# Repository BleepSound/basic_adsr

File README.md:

# Basic ADSR

Basic ADSR based on René Schmitz [Fastest envelope in the West](https://www.schmitzbits.de/adsr.html). 

Four pots, one input, one output (just what you need).

On switch to change the time constant of the ADSR. I chose some arbitrary values for the capacitors in my case, but if you want different values, you can adjust them to your needs. 

Just change the values of **C8** and **C9**, which can be either polarized electrolytic or unpolarized capacitors. Just make sure you get the orientation right on the polarized ones.

## Schematics

## BoM

[See bom](documentation/bom/Basic-ADSR_V1.0--iBoM.html)

## Build Informations

Regular build, I use ceramic capacitors but you can use film/polyester.

:warning: When building modules, always do it in this order (from smallest component to highest):
- diodes
- resistors
- DIP chips
- capacitors (film/ceramic)
- Transistors
- Electrolytic capacitors

To solder the headers, place them and place both PCBs in their final position before fully soldering the pin headers/sockets.

For the next parts, always place them without soldering them on: 
- jacks, pots and switches that go throught the front panel

Once placed, put the front panel in place, then fasten all components to it. Once this is done, you can solder all the remaining components.

## Images

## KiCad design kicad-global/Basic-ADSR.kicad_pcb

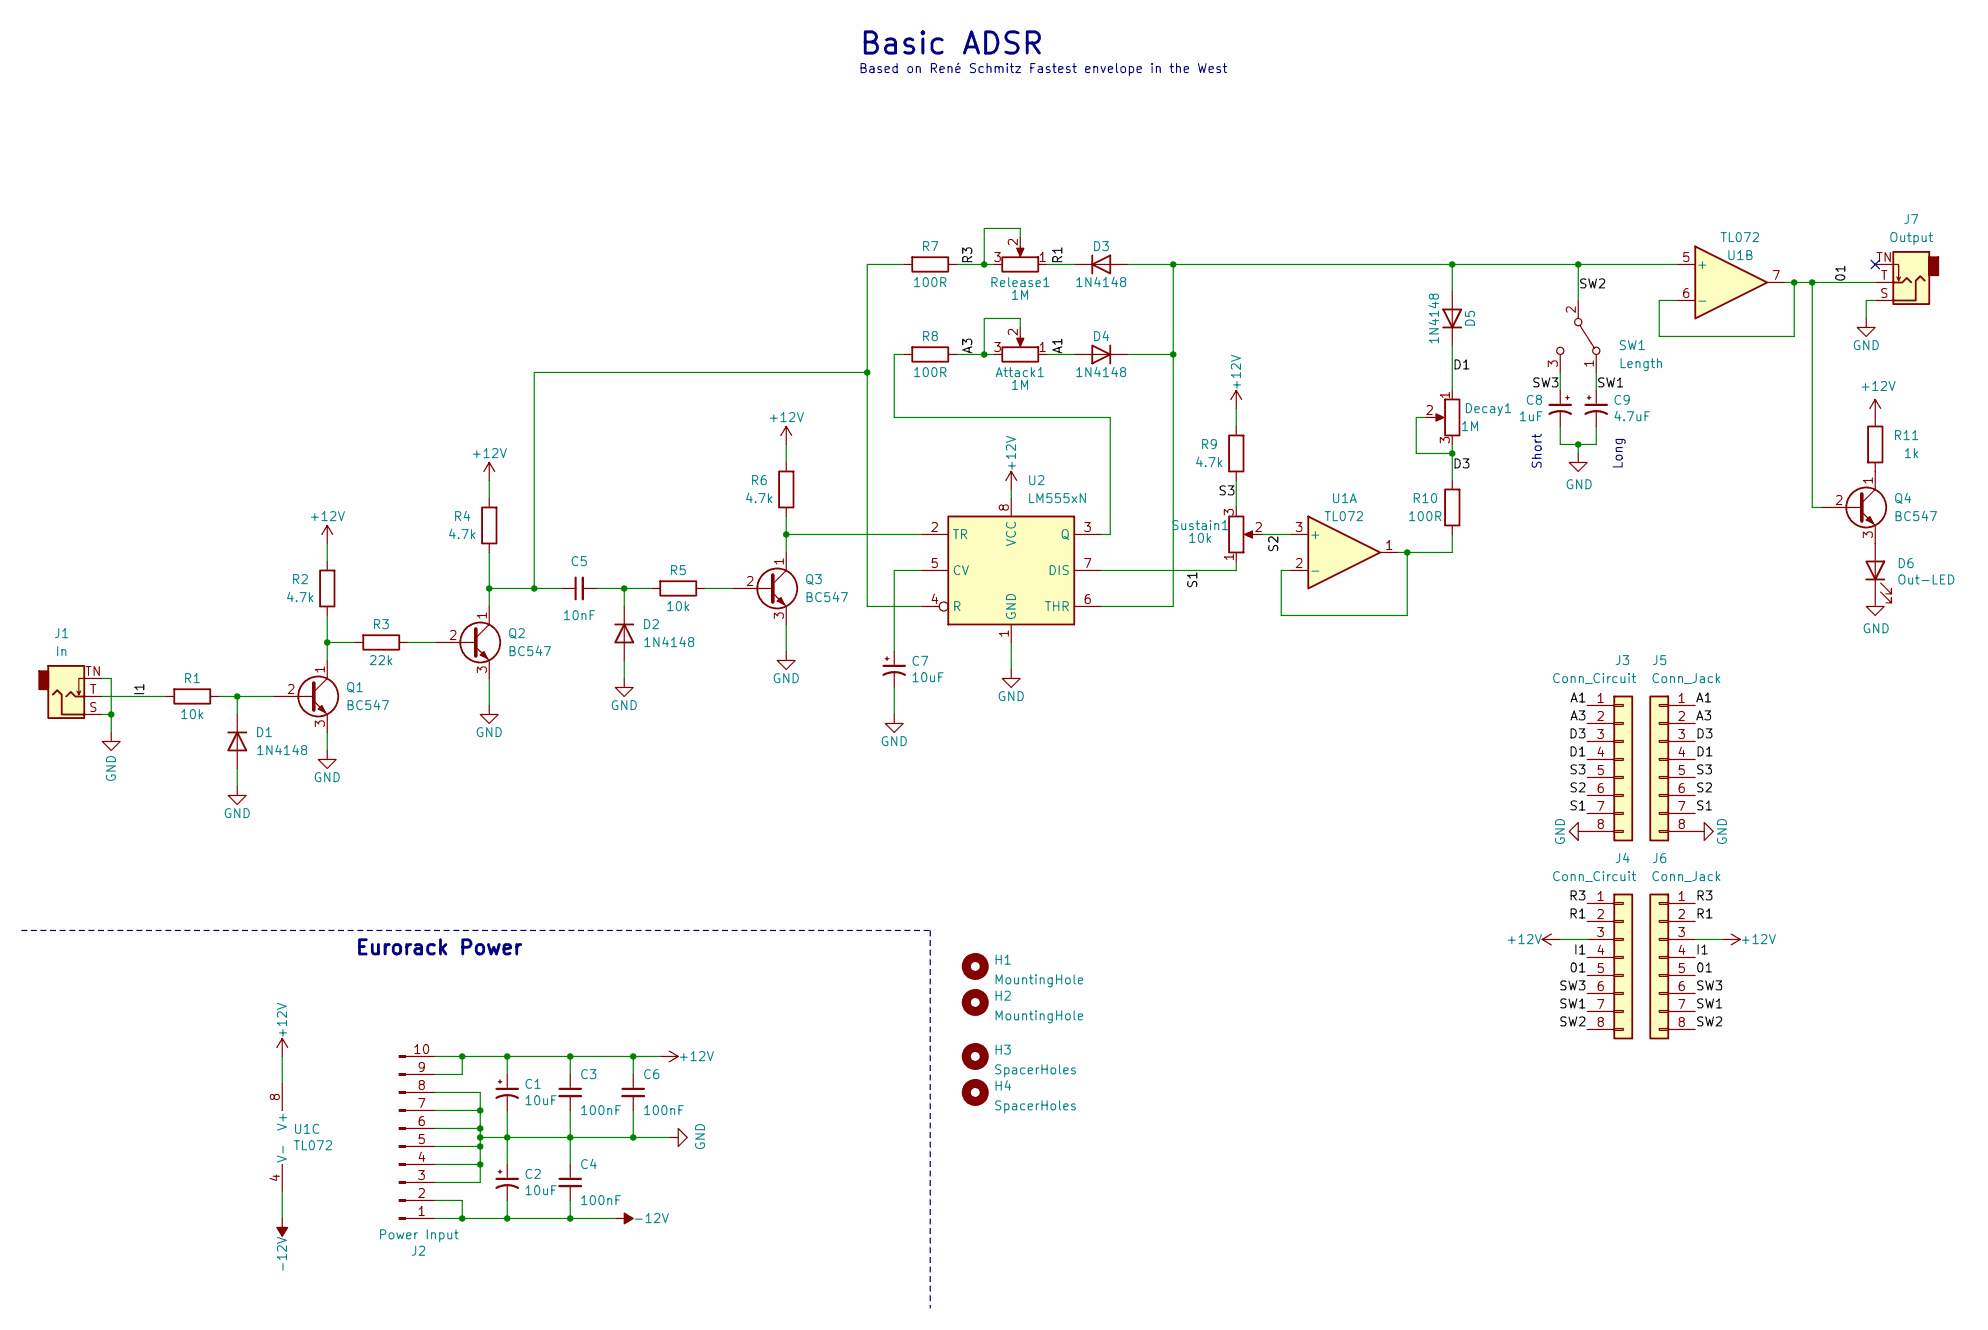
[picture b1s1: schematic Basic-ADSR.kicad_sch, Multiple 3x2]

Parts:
Attack1: 1M; Pot-bourns-alpha
C1, C2, C7: 10uF; CP_Radial_D5.0mm_P2.00mm
C3, C4, C6: 100nF; C_Disc_D7.0mm_W2.5mm_P5.00mm
C5: 10nF; C_Disc_D7.0mm_W2.5mm_P5.00mm
C8: 1uF; CP_Radial_D5.0mm_P2.00mm
C9: 4.7uF; CP_Radial_D5.0mm_P2.00mm
D1, D2, D3, D4, D5: 1N4148; D_DO-35_SOD27_P7.62mm_Horizontal
D6: Out-LED; LED_D4.0mm
Decay1: 1M; Pot-bourns-alpha
H1, H2: MountingHole; Doepfer Mounting hole
H3, H4: SpacerHoles; MountingHole_3.2mm_M3
J1: In; Thonkiconn
J2: Power Input; IDC-Header_2x05_P2.54mm_Vertical
J3, J4: Conn_Circuit; PinSocket_1x08_P2.54mm_Vertical
J5, J6: Conn_Jack; PinHeader_1x08_P2.54mm_Vertical
J7: Output; Thonkiconn
Q1, Q2, Q3, Q4: BC547; TO-92_Inline
R1, R5: 10k; R_Axial_DIN0207_L6.3mm_D2.5mm_P10.16mm_Horizontal
R2, R4, R6, R9: 4.7k; R_Axial_DIN0207_L6.3mm_D2.5mm_P10.16mm_Horizontal
R3: 22k; R_Axial_DIN0207_L6.3mm_D2.5mm_P10.16mm_Horizontal
R7, R8, R10: 100R; R_Axial_DIN0207_L6.3mm_D2.5mm_P10.16mm_Horizontal
R11: 1k; R_Axial_DIN0207_L6.3mm_D2.5mm_P10.16mm_Horizontal
Release1: 1M; Pot-bourns-alpha
SW1: Length; SW_Toggle_Blue_wSlots
Sustain1: 10k; Pot-bourns-alpha
U1: TL072; DIP-8_W7.62mm_Socket
U2: LM555xN; DIP-8_W7.62mm

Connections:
+12V: C1.1, C3.1, C6.1, J2.9, J2.10, J4.3, J6.3, R2.2, R4.2, R6.2, R9.2, R11.1, U1.8 (V+), U2.8 (VCC)
-12V: C2.2, C4.2, J2.1, J2.2, U1.4 (V-)
/01: J4.5, J6.5, J7.T, Q4.2 (B), U1.6 (-), U1.7
/A1: Attack1.1, D4.2 (A), J3.1, J5.1
/A3: Attack1.2, Attack1.3, J3.2, J5.2, R8.1
/D1: D5.1 (K), Decay1.1, J3.4, J5.4
/D3: Decay1.2, Decay1.3, J3.3, J5.3, R10.2
/I1: J1.T, J4.4, J6.4, R1.2
/R1: D3.1 (K), J4.2, J6.2, Release1.1
/R3: J4.1, J6.1, R7.1, Release1.2, Release1.3
/S1: J3.7, J5.7, Sustain1.1, U2.7 (DIS)
/S2: J3.6, J5.6, Sustain1.2, U1.3 (+)
/S3: J3.5, J5.5, R9.1, Sustain1.3
/SW1: C9.1, J4.7, J6.7, SW1.1 (A)
/SW2: D3.2 (A), D4.1 (K), D5.2 (A), J4.8, J6.8, SW1.2 (B), U1.5 (+), U2.6 (THR)
/SW3: C8.1, J4.6, J6.6, SW1.3 (C)
GND: C1.2, C2.1, C3.2, C4.1, C6.2, C7.2, C8.2, C9.2, D1.2 (A), D2.2 (A), D6.1 (K), J1.S, J1.TN, J2.3, J2.4, J2.5, J2.6, J2.7, J2.8, J3.8, J5.8, J7.S, Q1.3 (E), Q2.3 (E), Q3.3 (E), U2.1 (GND)
unnamed: D1.1 (K), Q1.2 (B), R1.1
unnamed: C5.2, D2.1 (K), R5.2
unnamed: D6.2 (A), Q4.3 (E)
unnamed: Q1.1 (C), R2.1, R3.2
unnamed: Q2.2 (B), R3.1
unnamed: C5.1, Q2.1 (C), R4.1, R7.2, U2.4 (R)
unnamed: Q3.2 (B), R5.1
unnamed: Q3.1 (C), R6.1, U2.2 (TR)
unnamed: Q4.1 (C), R11.2
unnamed: R10.1, U1.1, U1.2 (-)
unnamed: C7.1, U2.5 (CV)
unnamed: R8.2, U2.3 (Q)

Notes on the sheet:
Based on René Schmitz Fastest envelope in the West
Long
Basic ADSR
Eurorack Power
Short

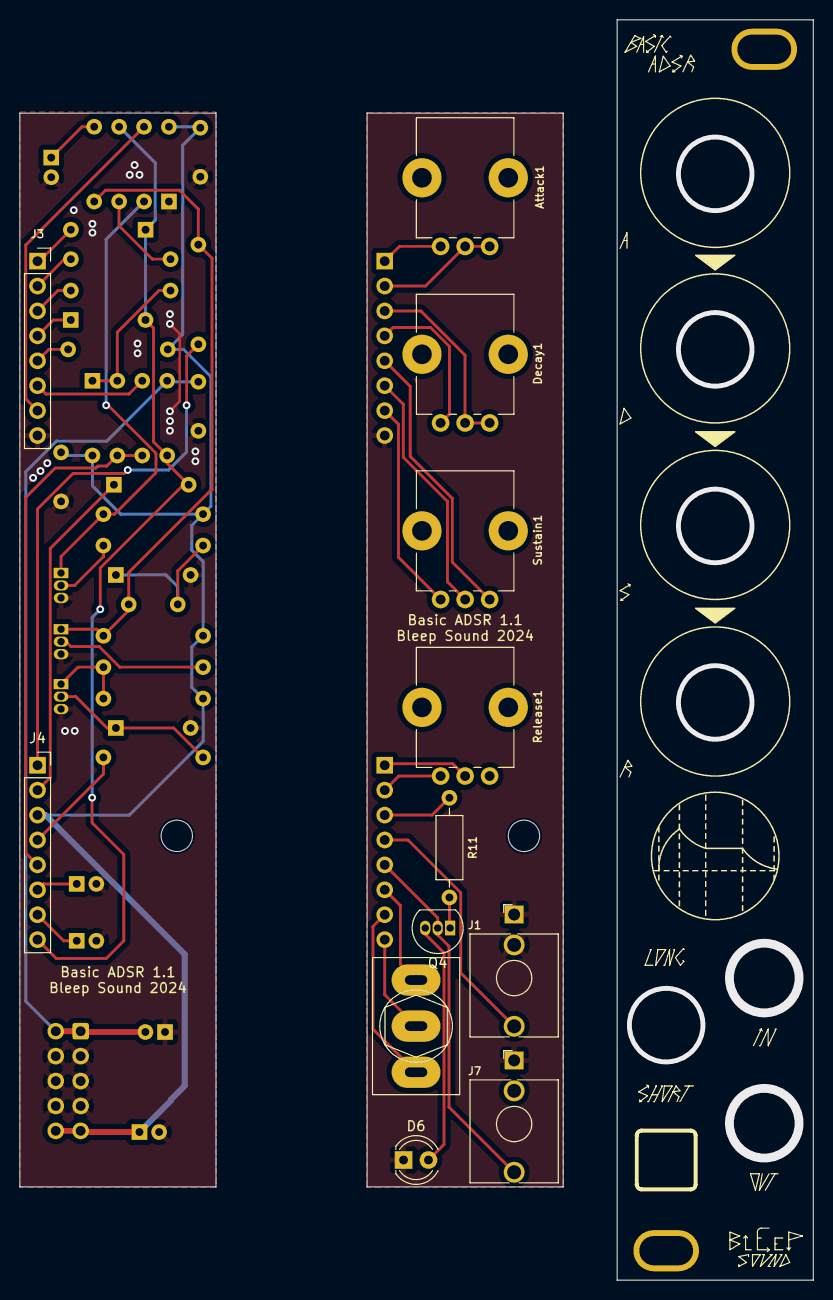
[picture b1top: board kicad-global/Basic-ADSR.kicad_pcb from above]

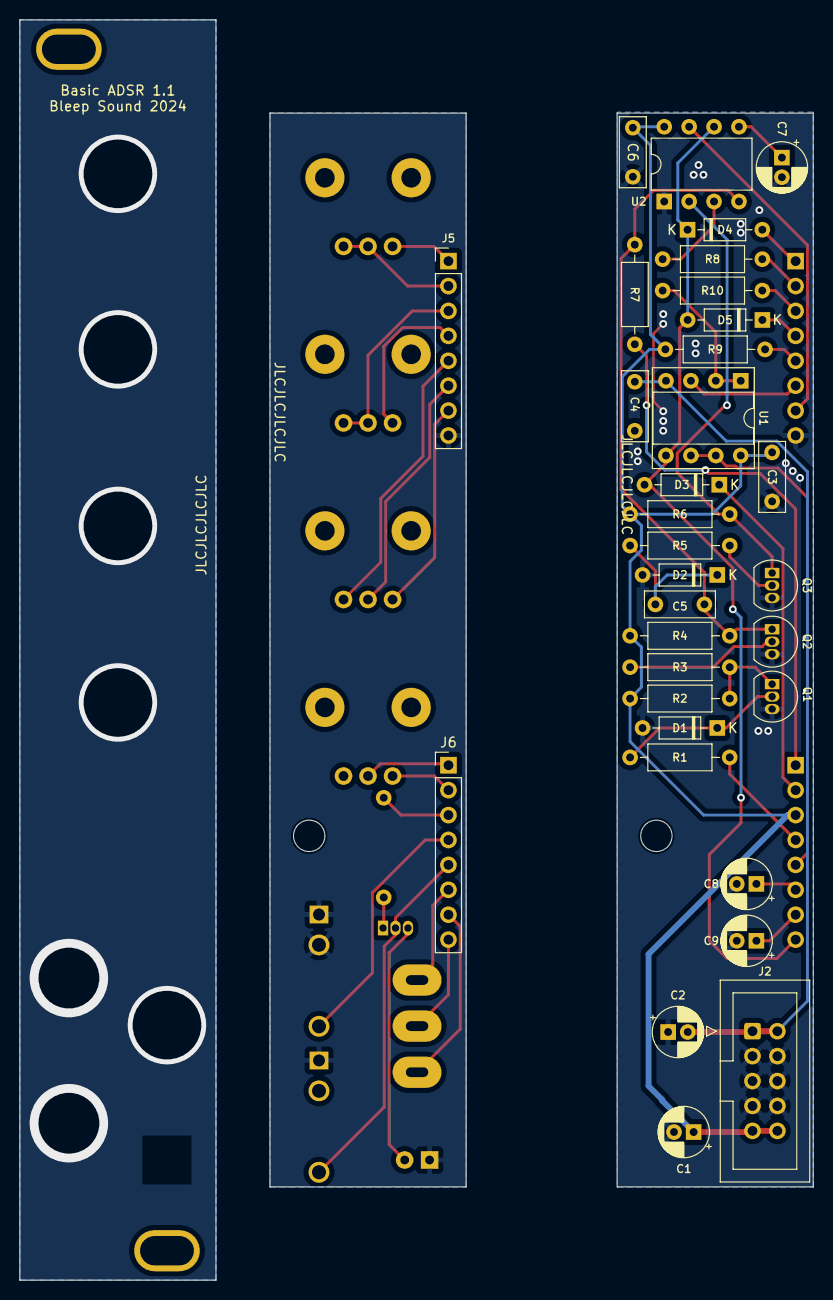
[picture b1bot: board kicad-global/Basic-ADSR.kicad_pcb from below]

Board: 2 copper layers, 80.9 x 128.5 mm, 48 parts (32 on the bottom side), 29 nets.

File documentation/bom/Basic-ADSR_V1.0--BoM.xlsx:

Basic-ADSR_V1.0 Bill of Materials
Schematic: | Basic-ADSR | Component Groups: | 23
Variant: | default | Component Count: | 44 (0 SMD/ 44 THT)
Revision: | 1.0 | Fitted Components: | 44 (0 SMD/ 44 THT)
Date: | 2023-09-23 | Number of PCBs: | 1
KiCad Version: | 7.0.7-7.0.7~ubuntu22.04.1 | Total Components: | 44
Row | Description | References | Value | Quantity Per PCB | Comments
1 | Potentiometer | Attack1 Decay1 Release1 | 1M | 3 | Pots
2 | Unpolarized capacitor, small symbol | C5 | 10nF | 1
3 | Unpolarized capacitor, small symbol | C3 C4 C6 | 100nF | 3
4 |  | C8 | 1uF | 1 | Radial electrolytic capacitors, can be changed to any value to change length
5 |  | C9 | 4.7uF | 1 | Radial electrolytic capacitors, can be changed to any value to change length
6 |  | C1 C2 C7 | 10uF | 3 | Radial electrolytic capacitors
7 | Diode | D1 D2 D3 D4 D5 | 1N4148 | 5
8 | Light emitting diode | D6 | Out-LED | 1
9 | Generic connector, single row, 01x08, script generated (kicad-library-utils/sch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 | J3 J4 | Conn_Circuit | 2
10 | Generic connector, single row, 01x08, script generated (kicad-library-utils/sch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 | J5 J6 | Conn_Jack | 2
11 | Thonkiconn Audio Jack | J1 | In | 1 | Thonkiconn jack
12 | Thonkiconn Audio Jack | J7 | Output | 1 | Thonkiconn jack
13 | Generic connector, single row, 01x10, script generated (kicad-library-utils/sch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 | J2 | Power Input | 1
14 | 0.1A Ic, 45V Vce, Small Signal NPN Transistor, TO-92 | Q1 Q2 Q3 Q4 | BC547 | 4 | Can use BC548
15 | Resistor | R7 R8 R10 | 100R | 3
16 | Resistor | R11 | 1k | 1
17 | Resistor | R2 R4 R6 R9 | 4.7k | 4
18 | Resistor | R1 R5 | 10k | 2
19 | Resistor | R3 | 22k | 1
20 | Switch, single pole double throw | SW1 | Length | 1 | SPDT On-On Switch
21 | Potentiometer | Sustain1 | 10k | 1 | Pots
22 | Timer, 555 compatible, PDIP-8 | U2 | LM555xN | 1
23 | Dual Low-Noise JFET-Input Operational Amplifiers, DIP-8/SOIC-8 | U1 | TL072 | 1

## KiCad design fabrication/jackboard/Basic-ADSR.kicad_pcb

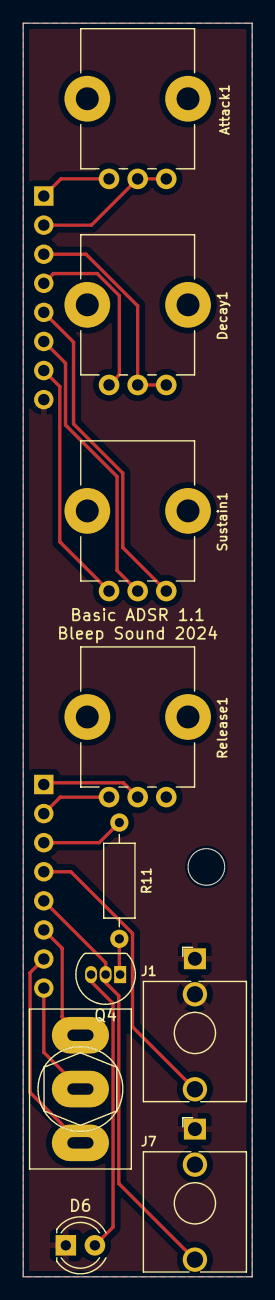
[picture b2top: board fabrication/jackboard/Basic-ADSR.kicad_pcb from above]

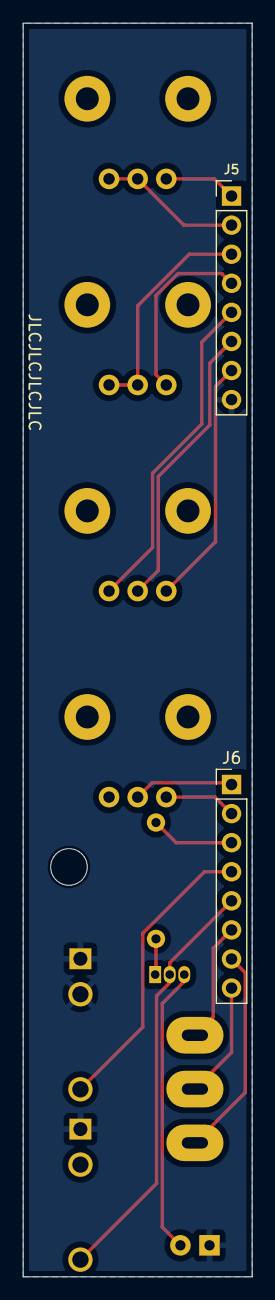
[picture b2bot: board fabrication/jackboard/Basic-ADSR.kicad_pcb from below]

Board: 2 copper layers, 20.0 x 109.5 mm, 13 parts (2 on the bottom side), 18 nets.

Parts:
Attack1: 1M; Pot-bourns-alpha
D6: Out-LED; LED_D4.0mm
Decay1: 1M; Pot-bourns-alpha
H3: SpacerHoles; MountingHole_3.2mm_M3
J1: In; Thonkiconn
J5, J6: Conn_Jack; PinHeader_1x08_P2.54mm_Vertical
J7: Output; Thonkiconn
Q4: BC547; TO-92_Inline
R11: 1k; R_Axial_DIN0207_L6.3mm_D2.5mm_P10.16mm_Horizontal
Release1: 1M; Pot-bourns-alpha
SW1: Length; SW_Toggle_Blue_wSlots
Sustain1: 10k; Pot-bourns-alpha

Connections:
+12V: J6.3, R11.1
/01: J6.5, J7.T, Q4.2 (B)
/A1: Attack1.1, J5.1
/A3: Attack1.2, Attack1.3, J5.2
/D1: Decay1.1, J5.4
/D3: Decay1.2, Decay1.3, J5.3
/I1: J1.T, J6.4
/R1: J6.2, Release1.1
/R3: J6.1, Release1.2, Release1.3
/S1: J5.7, Sustain1.1
/S2: J5.6, Sustain1.2
/S3: J5.5, Sustain1.3
/SW1: J6.7, SW1.1 (A)
/SW2: J6.8, SW1.2 (B)
/SW3: J6.6, SW1.3 (C)
GND: D6.1 (K), J1.S, J1.TN, J5.8, J7.S
unnamed: D6.2 (A), Q4.3 (E)
unnamed: Q4.1 (C), R11.2

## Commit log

2023-09-25 Full kicad files + fab files + Doc for ADSR
2023-10-11 update 3D view
2023-10-11 update link
2024-01-01 update GND plane for circuitboard following issues
